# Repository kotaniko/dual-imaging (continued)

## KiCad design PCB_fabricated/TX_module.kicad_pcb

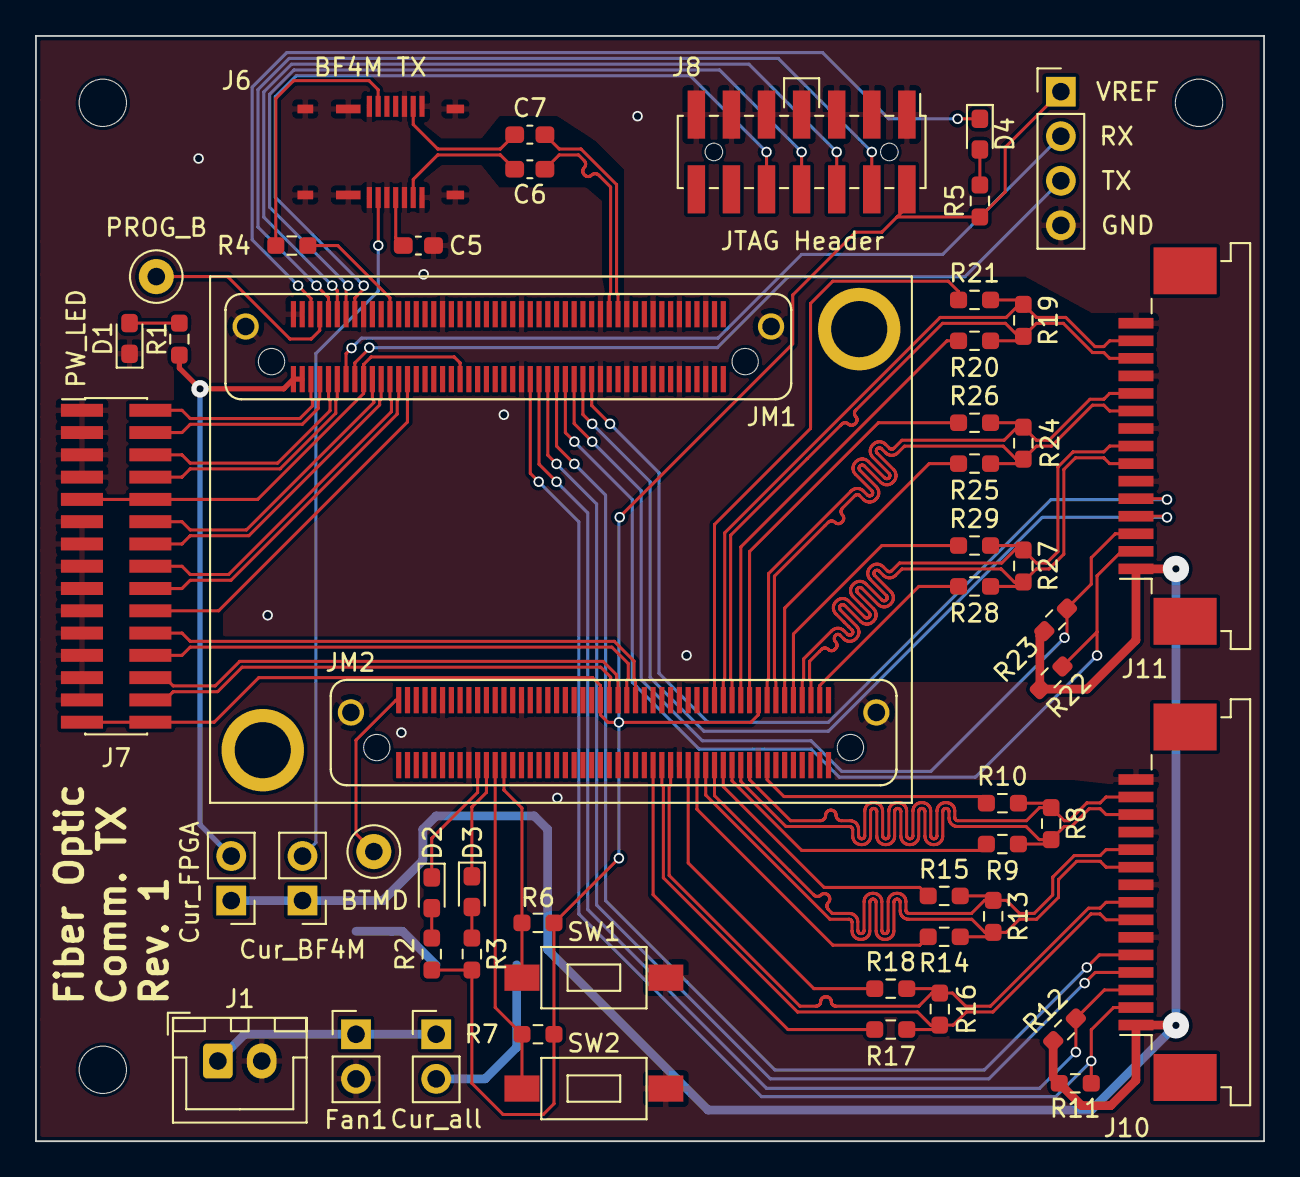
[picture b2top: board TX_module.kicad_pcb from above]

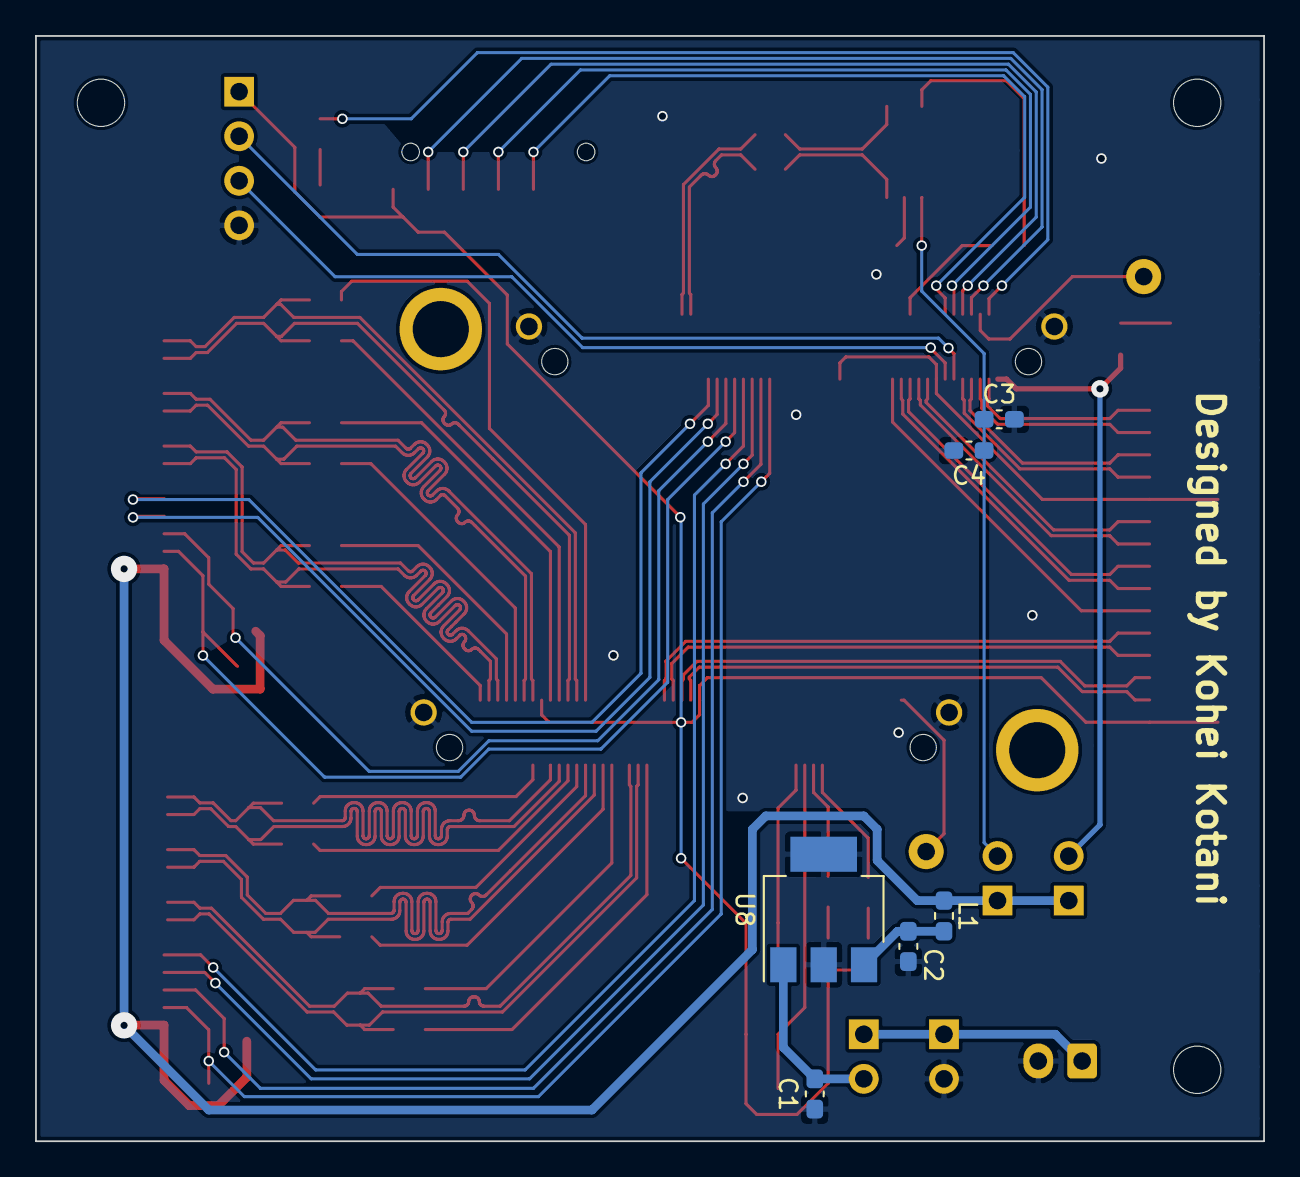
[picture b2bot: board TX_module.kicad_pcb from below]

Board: 2 copper layers, 70.0 x 63.0 mm, 58 parts (6 on the bottom side), 78 nets.

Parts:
C1, C2: 1uF; C_0603_1608Metric_Pad1.08x0.95mm_HandSolder
C3, C6, C7: 0.1uF; C_0603_1608Metric_Pad1.08x0.95mm_HandSolder
C4: 4.7uF; C_0603_1608Metric_Pad1.08x0.95mm_HandSolder
C5: 0.01uF; C_0603_1608Metric_Pad1.08x0.95mm_HandSolder
D1: LED Red; LED_0603_1608Metric_Pad1.05x0.95mm_HandSolder
D2, D4: LED Green; LED_0603_1608Metric_Pad1.05x0.95mm_HandSolder
D3: LED Yellow; LED_0603_1608Metric_Pad1.05x0.95mm_HandSolder
J1: Power_Conn; JST_XH_B2B-XH-A_1x02_P2.50mm_Vertical
J2: Fan1; PinHeader_1x02_P2.54mm_Vertical
J3, J4, J5: Cmeas; PinHeader_1x02_P2.54mm_Vertical
J6: BF4-TX-14DS-0.5V; BF4TX14DS05V
J7: Conn_02x15_Odd_Even; PinHeader_2x15_P1.27mm_Vertical_SMD
J8: JTAG Header; JTAG_Header
J9: UART_FPGA; PinHeader_1x04_P2.54mm_Vertical
J10, J11: FFC connector; TE_1-84953-5_1x15-1MP_P1.0mm_Horizontal
JM1: FPGA_module_B2B
L1: 1uH; L_0603_1608Metric_Pad1.05x0.95mm_HandSolder
R1: 1k; R_0603_1608Metric_Pad0.98x0.95mm_HandSolder
R2, R3, R5, R9, R10, R14, R15, R17, R18, R20, R21, R25, R26, R28, R29: 100; R_0603_1608Metric_Pad0.98x0.95mm_HandSolder
R4: 4.7k; R_0603_1608Metric_Pad0.98x0.95mm_HandSolder
R6, R7: 10k; R_0603_1608Metric_Pad0.98x0.95mm_HandSolder
R8, R13, R16, R19, R24, R27: 150; R_0603_1608Metric_Pad0.98x0.95mm_HandSolder
R11, R12, R22, R23: 1.5K; R_0603_1608Metric_Pad0.98x0.95mm_HandSolder
SW1: KEY0; SW_SPST_PTS636
SW2: KEY1; SW_SPST_PTS636
TP1: PROG_B; TestPoint_Loop_D2.50mm_Drill1.0mm
TP2: BOOTMODE; TestPoint_Loop_D2.50mm_Drill1.0mm
U8: TC1262-3.3V; SOT-223-3_TabPin2

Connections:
+3V3: J4.1, J5.1, J10.1, J11.1, L1.2, R11.2, R12.2, R22.2, R23.2
+5V: J1.1, J2.1, J3.1
/BF4M_EN: J6.17, R4.1
/DIN+: C6.2, J6.8
/DIN-: C7.2, J6.13
/FPGA module TX/1.8V: J7.29, J7.30, J8.2, J9.1, JM1.118, JM1.154, R2.2, R3.2, R5.1, R6.2, R7.2
/FPGA module TX/3.3V: J7.9, J7.10, JM1.61, JM1.83
/FPGA module TX/AURORA_TX_N: C7.1, JM1.26
/FPGA module TX/AURORA_TX_P: C6.1, JM1.28
/FPGA module TX/B14_L21_N: J7.2, JM1.95
/FPGA module TX/B14_L21_P: J7.4, JM1.93
/FPGA module TX/B14_L23_N: J7.8, JM1.89
/FPGA module TX/B14_L23_P: J7.6, JM1.91
/FPGA module TX/B15_L20_N: J7.26, JM1.150
/FPGA module TX/B15_L20_P: J7.28, JM1.152
/FPGA module TX/B15_L22_N: J7.22, JM1.146
/FPGA module TX/B15_L22_P: J7.24, JM1.148
/FPGA module TX/B34_L19_P: J7.20, JM1.73
/FPGA module TX/B34_L22_N: J7.18, JM1.75
/FPGA module TX/B34_L22_P: J7.16, JM1.77
/FPGA module TX/B34_L23_N: J7.14, JM1.79
/FPGA module TX/B34_L23_P: J7.12, JM1.81
/FPGA module TX/KEY0: JM1.175, R6.1, SW1.1
/FPGA module TX/KEY1: JM1.177, R7.1, SW2.1
/FPGA module TX/LED0: D2.1, JM1.181
/FPGA module TX/LED1: D3.1, JM1.179
/FPGA module TX/TCK: J8.6, JM1.90
/FPGA module TX/TDI: J8.10, JM1.86
/FPGA module TX/TDO: J8.8, JM1.88
/FPGA module TX/TMS: J8.4, JM1.92
/FPGA module TX/UART_RX: J9.2, JM1.87
/FPGA module TX/UART_TX: J9.3, JM1.85
/FPGA module TX/VIN: J4.2, JM1.97, JM1.99, R1.2
/a6: JM1.123, R9.1
/a7: JM1.115, R10.1
/a8: JM1.131, R14.1
/a9: JM1.125, R15.1
/a10: JM1.141, R17.1
/a11: JM1.133, R18.1
/a12: J10.4, JM1.41
/a13: J10.3, JM1.43, R12.1
/a14: J10.2, JM1.45, R11.1
/a15: J10.5, JM1.39
/b6: JM1.122, R20.1
/b7: JM1.128, R21.1
/b8: JM1.112, R25.1
/b9: JM1.120, R26.1
/b10: JM1.104, R28.1
/b11: JM1.110, R29.1
/b12: J11.4, JM1.33
/b13: J11.3, JM1.35, R23.1
/b14: J11.2, JM1.37, R22.1
/b15: J11.5, JM1.31
GND: C1.2, C2.2, C3.2, C4.2, C5.2, D1.1, J1.2, J2.2, J6.1, J6.2, J6.3, J6.5, J6.7, J6.9, J6.10, J6.11, J6.12, J6.14, J6.18, J6.19, J6.20, J7.1, J7.3, J7.5, J7.7, J7.11, J7.13, J7.15, J7.17, J7.19, J7.21, J7.23, J7.25, J7.27, J8.1, J8.3, J8.5, J8.7, J8.9, J8.11, J8.13, J9.4, J10.6, J10.9, J10.12, J10.15, J11.6, J11.9, J11.12, J11.15, JM1.5, JM1.6, JM1.11, JM1.12, JM1.17, JM1.18, JM1.23, JM1.24, JM1.29, JM1.30, JM1.47, JM1.48, JM1.66, JM1.84, JM1.98, JM1.100, JM1.117, JM1.135, JM1.136, JM1.172, JM1.183, JM1.190, JM1.SH, SW1.2, SW2.2, U8.2
MIPI1_CLK_N: J10.8, JM1.137, R16.1, R18.2
MIPI1_CLK_P: J10.7, JM1.139, R16.2, R17.2
MIPI1_LANE0_N: J10.14, JM1.119, R8.1, R10.2
MIPI1_LANE0_P: J10.13, JM1.121, R8.2, R9.2
MIPI1_LANE1_N: J10.11, JM1.127, R13.1, R15.2
MIPI1_LANE1_P: J10.10, JM1.129, R13.2, R14.2
MIPI2_CLK_N: J11.8, JM1.108, R27.1, R29.2
MIPI2_CLK_P: J11.7, JM1.106, R27.2, R28.2
MIPI2_LANE0_N: J11.14, JM1.126, R19.1, R21.2
MIPI2_LANE0_P: J11.13, JM1.124, R19.2, R20.2
MIPI2_LANE1_N: J11.11, JM1.116, R24.1, R26.2
MIPI2_LANE1_P: J11.10, JM1.114, R24.2, R25.2
unnamed: C1.1, J3.2, U8.1
unnamed: C2.1, L1.1, U8.3
unnamed: C3.1, C4.1, J5.2, J6.4
unnamed: C5.1, J6.6
unnamed: D1.2, R1.1
unnamed: D2.2, R2.1
unnamed: D3.2, R3.1
unnamed: D4.1, JM1.96
unnamed: D4.2, R5.2
unnamed: JM1.78, R4.2
unnamed: JM1.94, TP1.1
unnamed: JM1.200, TP2.1

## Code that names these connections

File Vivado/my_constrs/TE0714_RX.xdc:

set_property BITSTREAM.GENERAL.COMPRESS TRUE [current_design]
set_property BITSTREAM.CONFIG.CONFIGRATE 66 [current_design]
set_property BITSTREAM.CONFIG.SPI_32BIT_ADDR NO [current_design]
set_property BITSTREAM.CONFIG.SPI_BUSWIDTH 4 [current_design]
set_property BITSTREAM.CONFIG.M1PIN PULLNONE [current_design]
set_property BITSTREAM.CONFIG.M2PIN PULLNONE [current_design]
set_property BITSTREAM.CONFIG.M0PIN PULLNONE [current_design]
set_property BITSTREAM.CONFIG.USR_ACCESS TIMESTAMP [current_design]
set_property CONFIG_VOLTAGE 1.8 [current_design]
set_property CFGBVS GND [current_design]

set_property -dict {PACKAGE_PIN T14 IOSTANDARD LVCMOS18} [get_ports sys_clock]
set_property -dict {PACKAGE_PIN P18 IOSTANDARD LVCMOS18} [get_ports KEY0]
set_property -dict {PACKAGE_PIN T17 IOSTANDARD LVCMOS18} [get_ports KEY1]
set_property -dict {PACKAGE_PIN U10 IOSTANDARD LVCMOS18} [get_ports GPIO_O]
set_property -dict {PACKAGE_PIN V16 IOSTANDARD LVCMOS18} [get_ports {LED_YELLOW[0]}]
set_property -dict {PACKAGE_PIN V17 IOSTANDARD LVCMOS18} [get_ports {LED_GREEN[0]}]
set_property -dict {PACKAGE_PIN M15 IOSTANDARD LVCMOS18} [get_ports {EN_GTPWR[0]}]
set_property -dict {PACKAGE_PIN M6 IOSTANDARD LVCMOS33} [get_ports {PCIe_CLK_nREQ[0]}]
set_property -dict {PACKAGE_PIN R1 IOSTANDARD LVCMOS33} [get_ports PCIe_nRST]
set_property -dict {PACKAGE_PIN K18 IOSTANDARD LVCMOS18} [get_ports LED_MOD]
set_property PACKAGE_PIN B6 [get_ports {MGT_REFCLK_clk_p[0]}]
set_property PACKAGE_PIN E3 [get_ports {MGT_SERIAL_RX_rxn[0]}]
set_property PACKAGE_PIN D6 [get_ports {PCIe_REFCLK_clk_p[0]}]
set_property PACKAGE_PIN A3 [get_ports {PCIe_SERIAL_rxn[0]}]

set_false_path -from [get_ports KEY0]
set_input_delay 0.000 [get_ports KEY0]
set_false_path -from [get_ports KEY1]
set_input_delay 0 [get_ports KEY1]
set_false_path -from [get_ports PCIe_nRST]
set_input_delay 0 [get_ports PCIe_nRST]
set_false_path -to [get_ports {LED_YELLOW[0]}]
set_output_delay 0.000 [get_ports {LED_YELLOW[0]}]
set_false_path -to [get_ports {LED_GREEN[0]}]
set_output_delay 0.000 [get_ports {LED_GREEN[0]}]
set_false_path -to [get_ports LED_MOD]
set_output_delay 0 [get_ports LED_MOD]
set_false_path -to [get_ports {EN_GTPWR[0]}]
set_output_delay 0.000 [get_ports {EN_GTPWR[0]}]
set_false_path -to [get_ports {PCIe_CLK_nREQ[0]}]
set_output_delay 0 [get_ports {PCIe_CLK_nREQ[0]}]

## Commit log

2022-04-04 Add explanations on PCB/Schematic
2022-04-04 Add headings for the main readme
2022-04-24 RX PCB
2022-04-24 Add demo video
2022-04-24 Add video in readme
2022-04-24 Fix readme to embed video
2022-04-24 Add raspberry pi os submodule
2022-04-25 Fix image embed links
2022-04-25 Add images
2022-04-25 Reduce image size
